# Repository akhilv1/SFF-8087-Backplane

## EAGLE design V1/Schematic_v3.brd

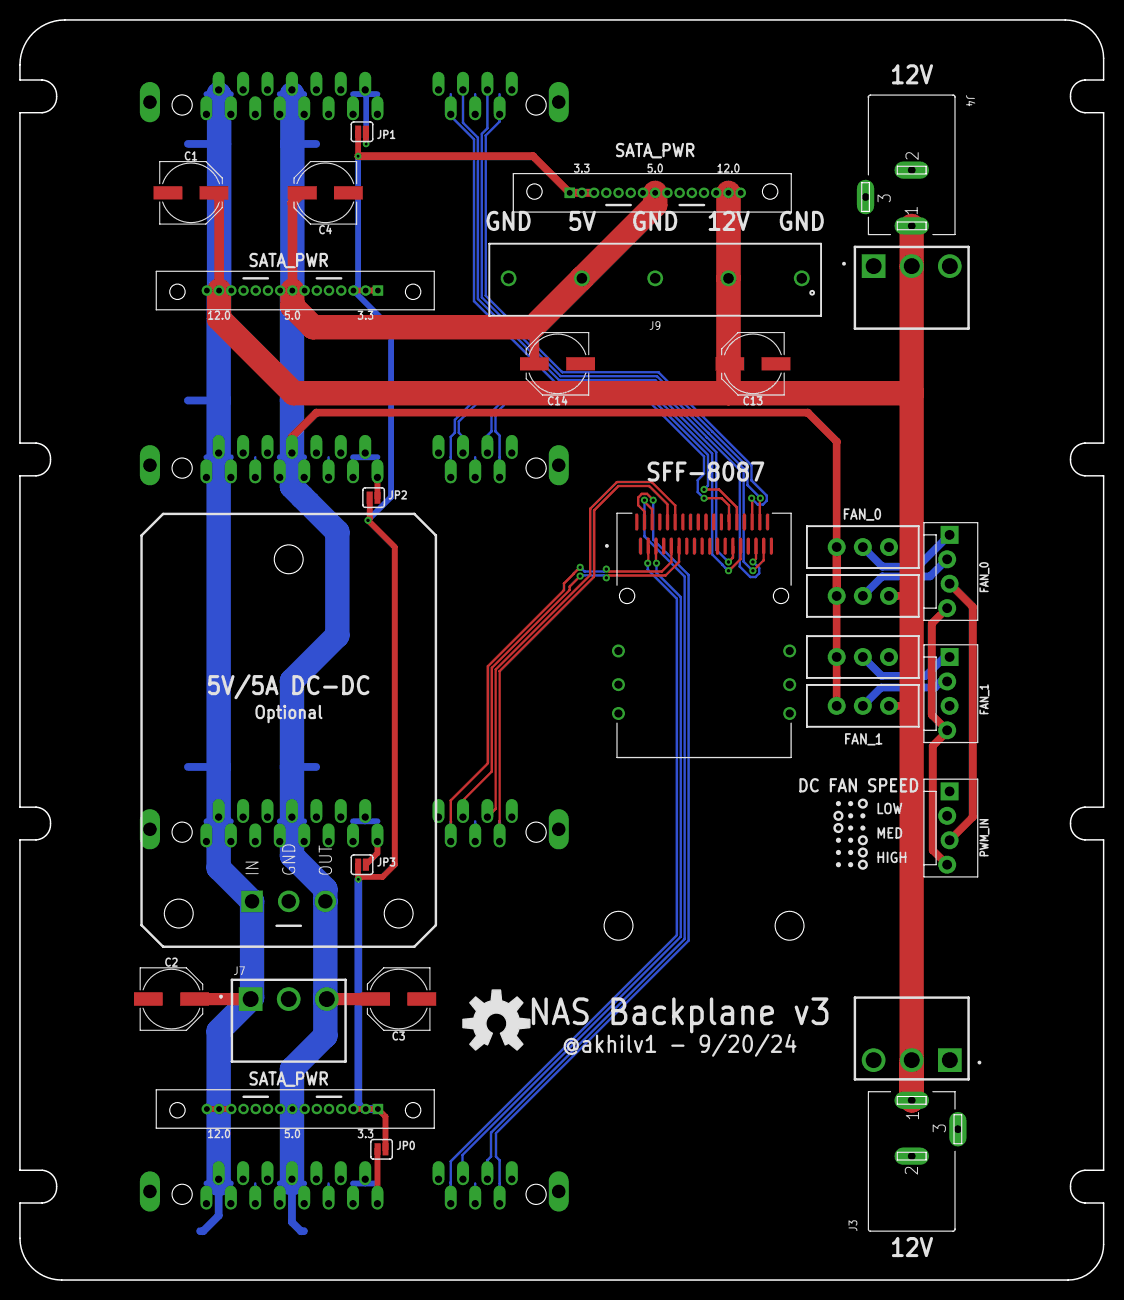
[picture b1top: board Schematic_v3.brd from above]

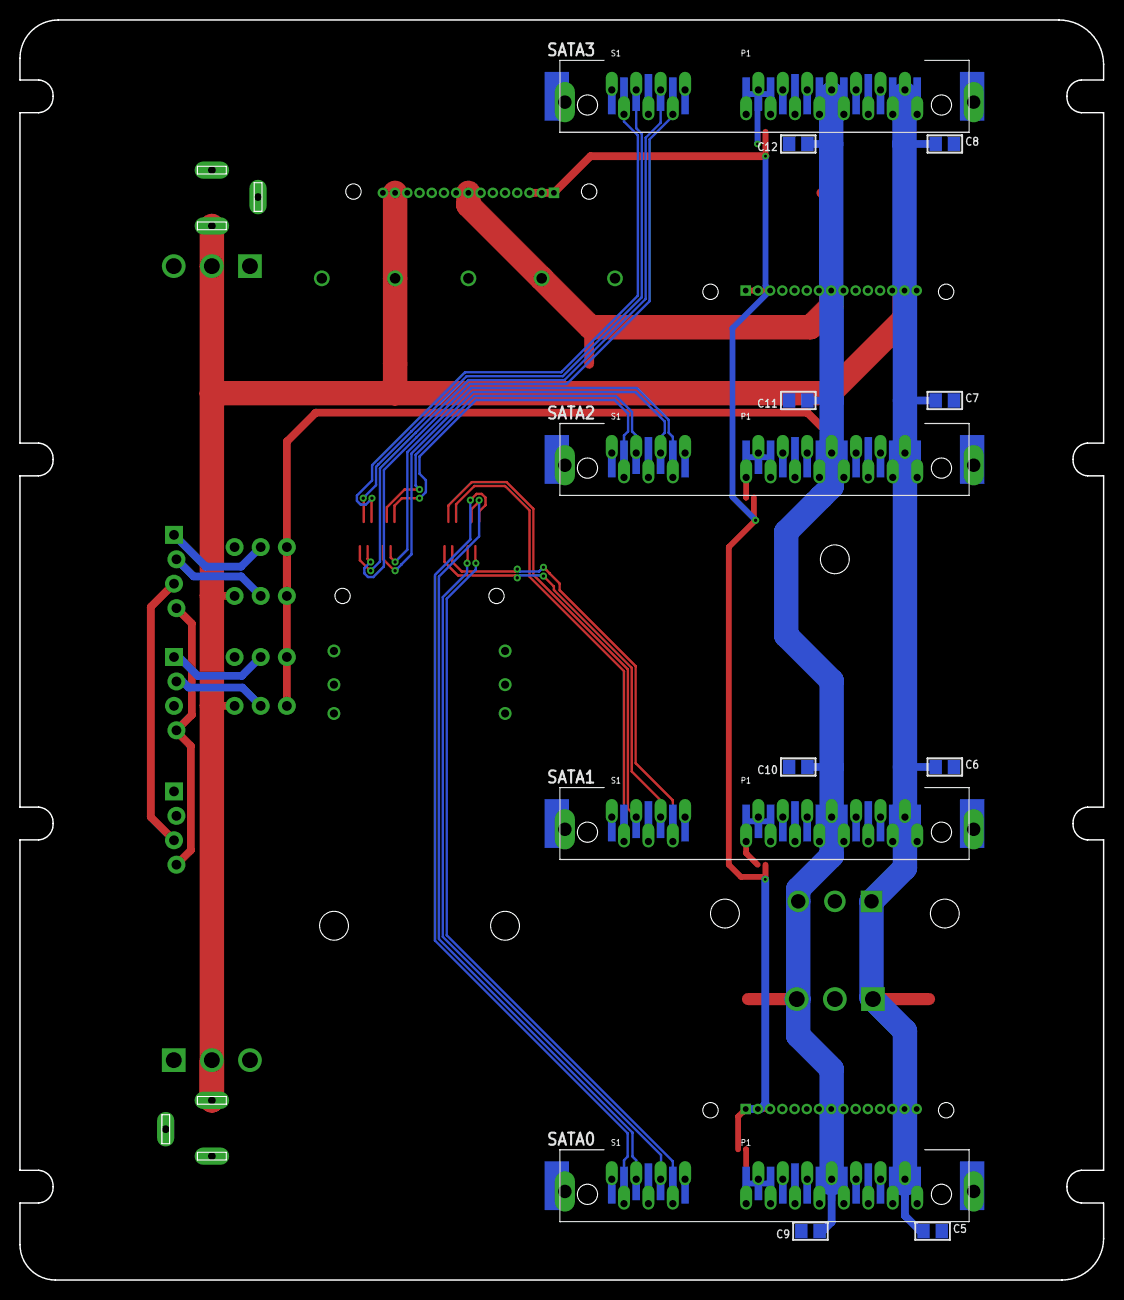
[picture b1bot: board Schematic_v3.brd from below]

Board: 2 copper layers, 112.7 x 131.0 mm, 41 parts (12 on the bottom side), 30 nets.

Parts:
C1, C2, C3, C4, C13, C14: 100uF; PANASONIC_D
C5, C6, C7, C8, C9, C10, C11, C12: C0805
FAN_0, FAN_1: MOLEX-1X4_LOCK
J1, J2, J8: SATAPWR; PTH_90
J3, J4: 694106301002
J5, J6, J7: B3P-VH(LF)(SN); HDR-03
J9: 691243410005
JP0, JP1, JP2, JP3: JUMPER-SMT_2_NC_PASTE_SILK; SMT-JUMPER_2_NC_PASTE_SILK
LOGO1: OSHW-LOGOL; OSHW-LOGO-L
PWM_IN: MOLEX-1X4_LOCK
S1, S2, S3, S4: SWITCH_SPDT_PTH_11.6X4.0MM_LOCK
SATA0, SATA1, SATA2, SATA3: 1735284-3; TE_2023246-2
SFF-8087: 1888019-4; TE_1888019-4
U$1: 5V_DC_DC; 5V_15W_DC_DC

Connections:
3.3V: J1.P$1, J1.P$2, J1.P$3, J2.P$1, J2.P$2, J2.P$3, J8.P$1, J8.P$2, J8.P$3, JP0.1, JP1.1, JP2.1, JP3.1
5V: C3.+, C4.+, C9.1, C10.1, C11.1, C12.1, C14.+, J1.P$7, J1.P$8, J1.P$9, J2.P$7, J2.P$8, J2.P$9, J7.3, J8.P$7, J8.P$8, J8.P$9, J9.4, S1.3, S2.1, S3.3, S4.1, SATA0.P7, SATA0.P8, SATA0.P9, SATA0.THT14, SATA0.THT15, SATA0.THT16, SATA1.P7, SATA1.P8, SATA1.P9, SATA1.THT14, SATA1.THT15, SATA1.THT16, SATA2.P7, SATA2.P8, SATA2.P9, SATA2.THT14, SATA2.THT15, SATA2.THT16, SATA3.P7, SATA3.P8, SATA3.P9, SATA3.THT14, SATA3.THT15, SATA3.THT16, U$1.P$3
12V: C1.+, C2.+, C5.1, C6.1, C7.1, C8.1, C13.+, J1.P$13, J1.P$14, J1.P$15, J2.P$13, J2.P$14, J2.P$15, J3.1, J4.1, J5.2, J6.2, J7.1, J8.P$13, J8.P$14, J8.P$15, J9.2, S1.1, S3.1, SATA0.P13, SATA0.P14, SATA0.P15, SATA0.THT20, SATA0.THT21, SATA0.THT22, SATA1.P13, SATA1.P14, SATA1.P15, SATA1.THT20, SATA1.THT21, SATA1.THT22, SATA2.P13, SATA2.P14, SATA2.P15, SATA2.THT20, SATA2.THT21, SATA2.THT22, SATA3.P13, SATA3.P14, SATA3.P15, SATA3.THT20, SATA3.THT21, SATA3.THT22, U$1.P$1
FAN0_HI: FAN_0.2, S1.2
FAN0_LO: FAN_0.1, S2.2
FAN1_HI: FAN_1.2, S3.2
FAN1_LO: FAN_1.1, S4.2
FAN_PWM: FAN_0.4, FAN_1.4, PWM_IN.4
FAN_TACH: FAN_0.3, PWM_IN.3
GND: C1.-, C2.-, C3.-, C4.-, C5.2, C6.2, C7.2, C8.2, C9.2, C10.2, C11.2, C12.2, C13.-, C14.-, J1.P$4, J1.P$5, J1.P$6, J1.P$10, J1.P$11, J1.P$12, J2.P$4, J2.P$5, J2.P$6, J2.P$10, J2.P$11, J2.P$12, J3.2, J4.2, J5.1, J5.3, J6.1, J6.3, J7.2, J8.P$4, J8.P$5, J8.P$6, J8.P$10, J8.P$11, J8.P$12, J9.1, J9.3, J9.5, PWM_IN.1, S2.3, S4.3, SATA0.P4, SATA0.P5, SATA0.P6, SATA0.P10, SATA0.P11, SATA0.P12, SATA0.P$1, SATA0.P$2, SATA0.S1, SATA0.S4, SATA0.S7, SATA0.THT1, SATA0.THT4, SATA0.THT7, SATA0.THT11, SATA0.THT12, SATA0.THT13, SATA0.THT17, SATA0.THT18, SATA0.THT19, SATA0.THT$1, SATA0.THT$2, SATA1.P4, SATA1.P5, SATA1.P6, SATA1.P10, SATA1.P11, SATA1.P12, SATA1.P$1, SATA1.P$2, SATA1.S1, SATA1.S4, SATA1.S7, SATA1.THT1, SATA1.THT4, SATA1.THT7, SATA1.THT11, SATA1.THT12, SATA1.THT13, SATA1.THT17, SATA1.THT18, SATA1.THT19, SATA1.THT$1, SATA1.THT$2, SATA2.P4, SATA2.P5, SATA2.P6, SATA2.P10, SATA2.P11, SATA2.P12, SATA2.P$1, SATA2.P$2, SATA2.S1, SATA2.S4, SATA2.S7, SATA2.THT1, SATA2.THT4, SATA2.THT7, SATA2.THT11, SATA2.THT12, SATA2.THT13, SATA2.THT17, SATA2.THT18, SATA2.THT19, SATA2.THT$1, SATA2.THT$2, SATA3.P4, SATA3.P5, SATA3.P6, SATA3.P10, SATA3.P11, SATA3.P12, SATA3.P$1, SATA3.P$2, SATA3.S1, SATA3.S4, SATA3.S7, SATA3.THT1, SATA3.THT4, SATA3.THT7, SATA3.THT11, SATA3.THT12, SATA3.THT13, SATA3.THT17, SATA3.THT18, SATA3.THT19, SATA3.THT$1, SATA3.THT$2, SFF-8087.A1, SFF-8087.A4, SFF-8087.A7, SFF-8087.A12, SFF-8087.A15, SFF-8087.A18, SFF-8087.B1, SFF-8087.B4, SFF-8087.B7, SFF-8087.B12, SFF-8087.B15, SFF-8087.B18, SFF-8087.S1, SFF-8087.S2, SFF-8087.S3, SFF-8087.S4, SFF-8087.S5, SFF-8087.S6, U$1.P$2
unnamed: JP1.2, SATA3.P1, SATA3.P2, SATA3.P3, SATA3.THT8, SATA3.THT9, SATA3.THT10
unnamed: JP2.2, SATA2.P1, SATA2.P2, SATA2.P3, SATA2.THT8, SATA2.THT9, SATA2.THT10
unnamed: JP3.2, SATA1.P1, SATA1.P2, SATA1.P3, SATA1.THT8, SATA1.THT9, SATA1.THT10
unnamed: JP0.2, SATA0.P1, SATA0.P2, SATA0.P3, SATA0.THT8, SATA0.THT9, SATA0.THT10
RX0_N: SATA0.S5, SATA0.THT5, SFF-8087.A3
RX0_P: SATA0.S6, SATA0.THT6, SFF-8087.A2
RX1_N: SATA1.S5, SATA1.THT5, SFF-8087.A6
RX1_P: SATA1.S6, SATA1.THT6, SFF-8087.A5
RX2_N: SATA2.S5, SATA2.THT5, SFF-8087.A14
RX2_P: SATA2.S6, SATA2.THT6, SFF-8087.A13
RX3_N: SATA3.S5, SATA3.THT5, SFF-8087.A17
RX3_P: SATA3.S6, SATA3.THT6, SFF-8087.A16
TX0_N: SATA0.S3, SATA0.THT3, SFF-8087.B3
TX0_P: SATA0.S2, SATA0.THT2, SFF-8087.B2
TX1_N: SATA1.S3, SATA1.THT3, SFF-8087.B6
TX1_P: SATA1.S2, SATA1.THT2, SFF-8087.B5
TX2_N: SATA2.S3, SATA2.THT3, SFF-8087.B14
TX2_P: SATA2.S2, SATA2.THT2, SFF-8087.B13
TX3_N: SATA3.S3, SATA3.THT3, SFF-8087.B17
TX3_P: SATA3.S2, SATA3.THT2, SFF-8087.B16

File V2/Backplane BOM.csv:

Qty,Value,Device,Parts,Description,Link
1,691243410005    ,691243410005    ,J9,7.62mm Pitch Rising Clamp Connector,
8,10uF,CAP_CERAMIC0805,"C5, C6, C7, C8, C9, C10, C11, C12",SMD Capacitors 0805 10uF,
3,,CONN_04POLAR_LOCK,"FAN_0, FAN_1, PWM_IN",Fan Headers 2.54mm Pitch,
4,,SWITCH-SPDT-PTH-11.6X4.0MM-LOCK,"S1, S2, S3, S4",Fan Mode Switches,
6,100uF,100UF-POLAR-25V-20%(ELEC),"C1, C2, C3, C4, C13, C14",100uF Electrolytic Capacitors,
4,1735284-3,TE_1735284-2,"SATA0, SATA1, SATA2, SATA3",Right Angle SATA Connectors,https://a.aliexpress.com/_mtHZzUZ
1,1888019-4,TE_1888019-4,SFF-8087,SFF-8087 SMD Connector,
1,39301060,39301060,POWER,Molex Mini-Fit JR 6-pin 90Deg,
1,5V_DC_DC,5V_DC_DC,BUCK,5v Step Down Converter (12v only input configuration),https://a.aliexpress.com/_mOm8TaH
1,694106301002    ,694106301002    ,J4,DC Barrel Power Jack 6.4mm Diam,
2,B3P-VH(LF)(SN),B3P-VH(LF)(SN),"J5, J7",JST-VH Connectors,
3,SATAPWR,SATAPWR,"J1, J2, J8",SATA Power Input Through Hole,https://a.aliexpress.com/_msddJj7

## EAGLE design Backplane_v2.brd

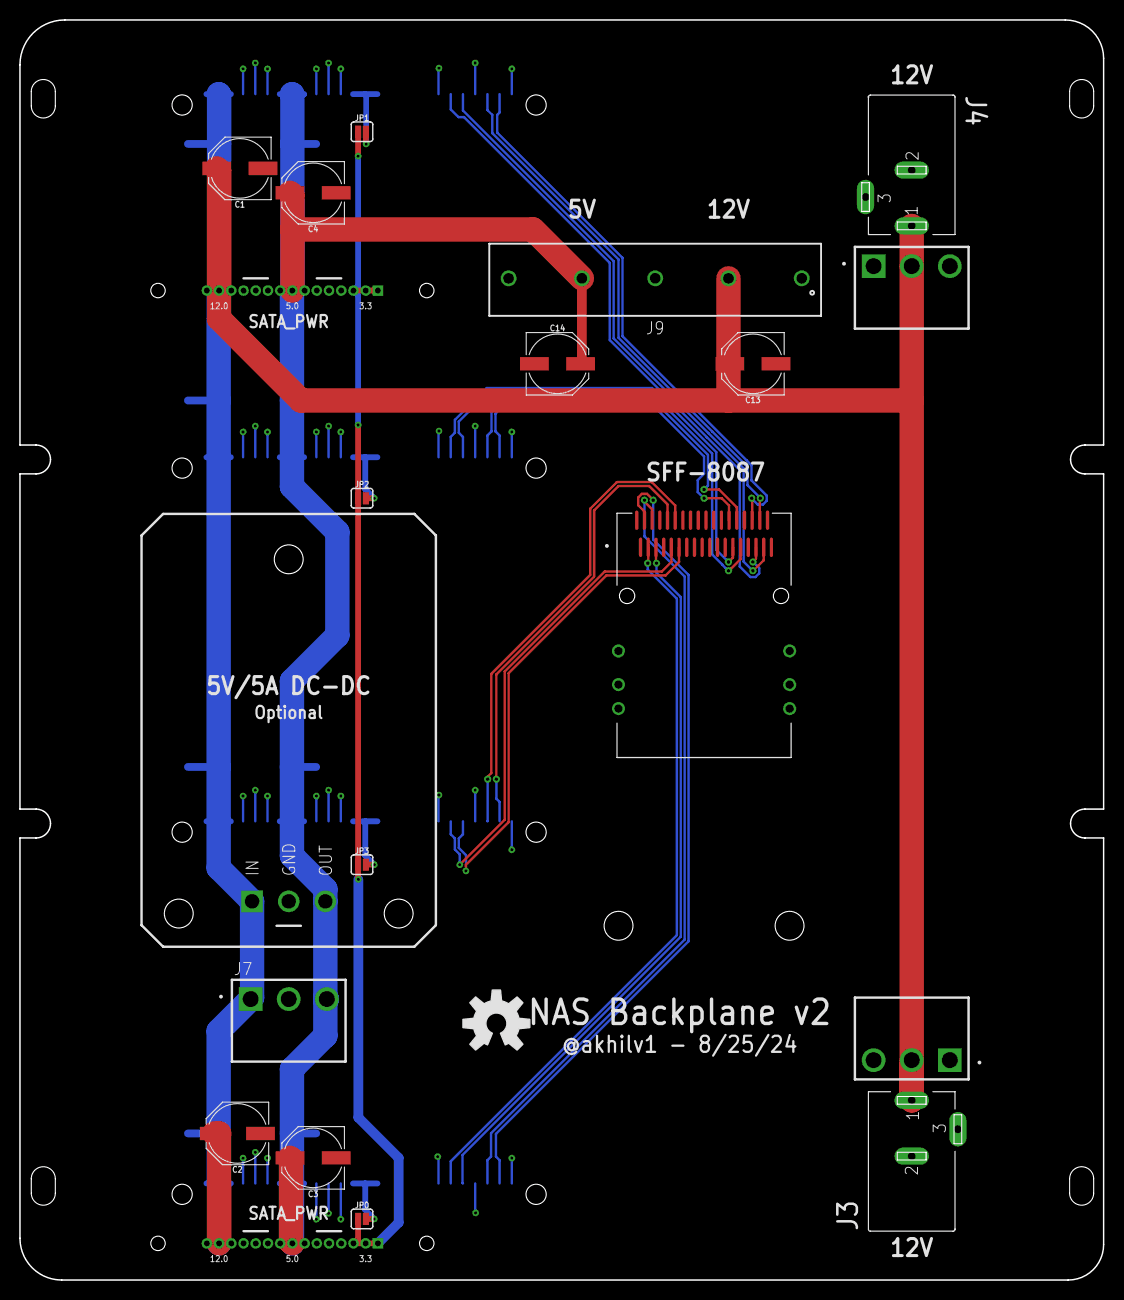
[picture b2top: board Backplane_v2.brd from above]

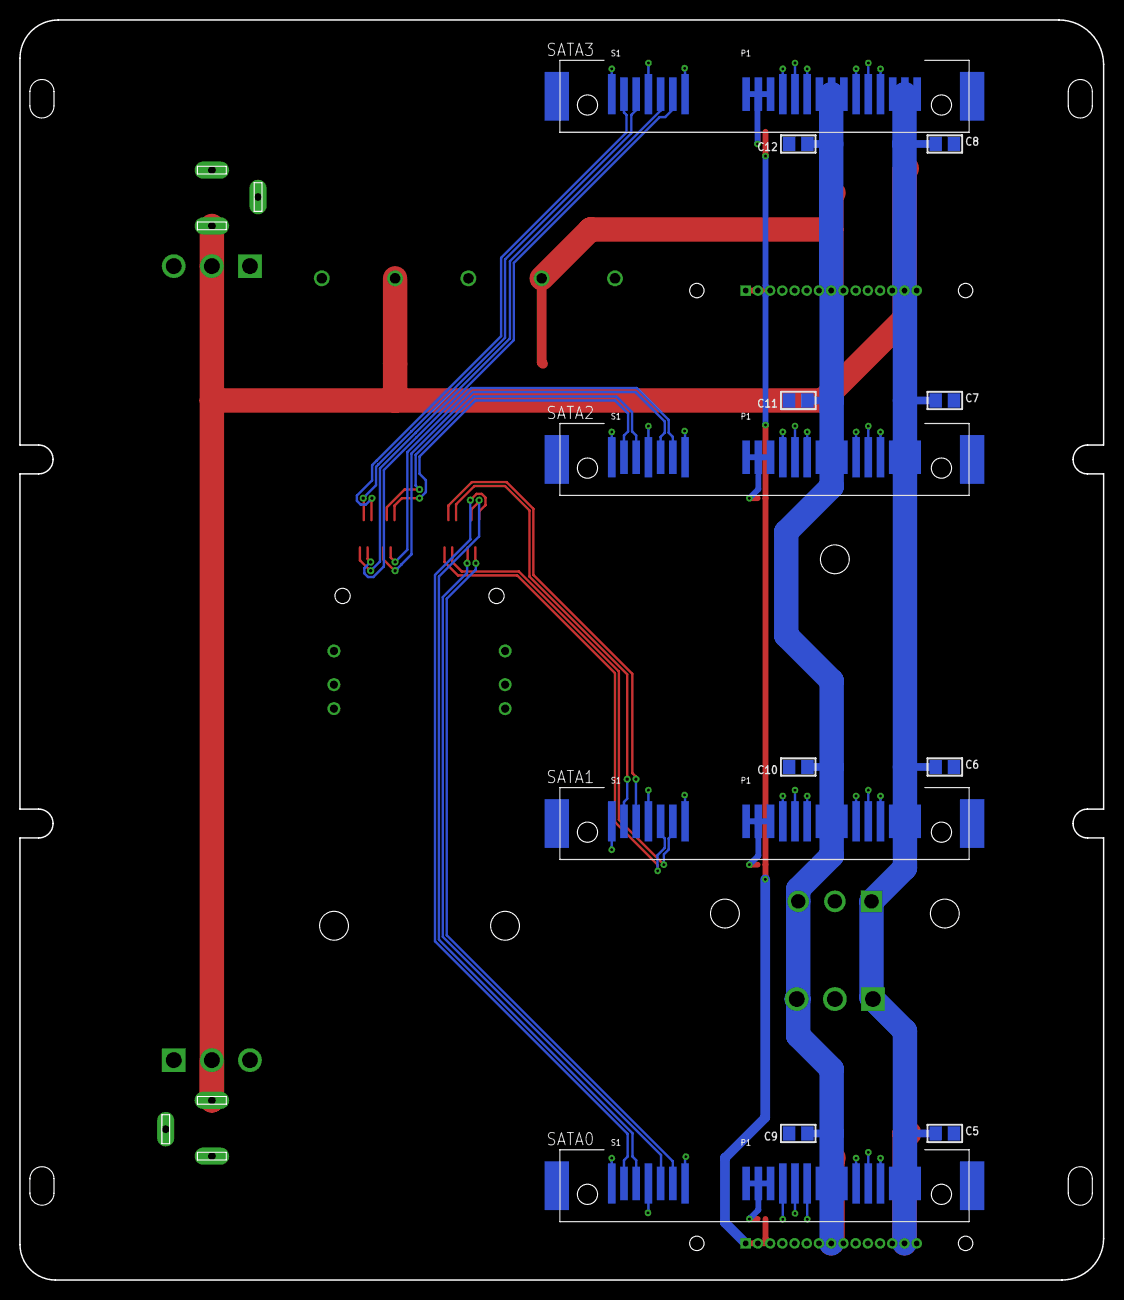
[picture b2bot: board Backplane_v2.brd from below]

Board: 2 copper layers, 112.7 x 131.0 mm, 33 parts (12 on the bottom side), 24 nets.

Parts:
C1, C2, C3, C4, C13, C14: 100uF; PANASONIC_D
C5, C6, C7, C8, C9, C10, C11, C12: C0805
J1, J2: SATAPWR; PTH_90
J3, J4: 694106301002
J5, J6, J7: B3P-VH(LF)(SN); HDR-03
J9: 691243410005
JP0, JP1, JP2, JP3: JUMPER-SMT_2_NC_PASTE_SILK; SMT-JUMPER_2_NC_PASTE_SILK
LOGO1: OSHW-LOGOL; OSHW-LOGO-L
SATA0, SATA1, SATA2, SATA3: 1735284-3; TE_2023246-2
SFF-8087: 1888019-4; TE_1888019-4
U$1: 5V_DC_DC; 5V_15W_DC_DC

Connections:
3.3V: J1.P$1, J1.P$2, J1.P$3, J2.P$1, J2.P$2, J2.P$3, JP0.1, JP1.1, JP2.1, JP3.1
5V: C3.+, C4.+, C9.1, C10.1, C11.1, C12.1, C14.+, J1.P$7, J1.P$8, J1.P$9, J2.P$7, J2.P$8, J2.P$9, J7.3, J9.4, SATA0.P7, SATA0.P8, SATA0.P9, SATA1.P7, SATA1.P8, SATA1.P9, SATA2.P7, SATA2.P8, SATA2.P9, SATA3.P7, SATA3.P8, SATA3.P9, U$1.P$3
12V: C1.+, C2.+, C5.1, C6.1, C7.1, C8.1, C13.+, J1.P$13, J1.P$14, J1.P$15, J2.P$13, J2.P$14, J2.P$15, J3.1, J4.1, J5.2, J6.2, J7.1, J9.2, SATA0.P13, SATA0.P14, SATA0.P15, SATA1.P13, SATA1.P14, SATA1.P15, SATA2.P13, SATA2.P14, SATA2.P15, SATA3.P13, SATA3.P14, SATA3.P15, U$1.P$1
GND: C1.-, C2.-, C3.-, C4.-, C5.2, C6.2, C7.2, C8.2, C9.2, C10.2, C11.2, C12.2, C13.-, C14.-, J1.P$4, J1.P$5, J1.P$6, J1.P$10, J1.P$11, J1.P$12, J2.P$4, J2.P$5, J2.P$6, J2.P$10, J2.P$11, J2.P$12, J3.2, J4.2, J5.1, J5.3, J6.1, J6.3, J7.2, J9.1, J9.3, J9.5, SATA0.P4, SATA0.P5, SATA0.P6, SATA0.P10, SATA0.P11, SATA0.P12, SATA0.P$1, SATA0.P$2, SATA0.S1, SATA0.S4, SATA0.S7, SATA1.P4, SATA1.P5, SATA1.P6, SATA1.P10, SATA1.P11, SATA1.P12, SATA1.P$1, SATA1.P$2, SATA1.S1, SATA1.S4, SATA1.S7, SATA2.P4, SATA2.P5, SATA2.P6, SATA2.P10, SATA2.P11, SATA2.P12, SATA2.P$1, SATA2.P$2, SATA2.S1, SATA2.S4, SATA2.S7, SATA3.P4, SATA3.P5, SATA3.P6, SATA3.P10, SATA3.P11, SATA3.P12, SATA3.P$1, SATA3.P$2, SATA3.S1, SATA3.S4, SATA3.S7, SFF-8087.A1, SFF-8087.A4, SFF-8087.A7, SFF-8087.A12, SFF-8087.A15, SFF-8087.A18, SFF-8087.B1, SFF-8087.B4, SFF-8087.B7, SFF-8087.B12, SFF-8087.B15, SFF-8087.B18, SFF-8087.S1, SFF-8087.S2, SFF-8087.S3, SFF-8087.S4, SFF-8087.S5, SFF-8087.S6, U$1.P$2
unnamed: JP1.2, SATA3.P1, SATA3.P2, SATA3.P3
unnamed: JP2.2, SATA2.P1, SATA2.P2, SATA2.P3
unnamed: JP3.2, SATA1.P1, SATA1.P2, SATA1.P3
unnamed: JP0.2, SATA0.P1, SATA0.P2, SATA0.P3
RX0_N: SATA0.S5, SFF-8087.A3
RX0_P: SATA0.S6, SFF-8087.A2
RX1_N: SATA1.S5, SFF-8087.A6
RX1_P: SATA1.S6, SFF-8087.A5
RX2_N: SATA2.S5, SFF-8087.A14
RX2_P: SATA2.S6, SFF-8087.A13
RX3_N: SATA3.S5, SFF-8087.A17
RX3_P: SATA3.S6, SFF-8087.A16
TX0_N: SATA0.S3, SFF-8087.B3
TX0_P: SATA0.S2, SFF-8087.B2
TX1_N: SATA1.S3, SFF-8087.B6
TX1_P: SATA1.S2, SFF-8087.B5
TX2_N: SATA2.S3, SFF-8087.B14
TX2_P: SATA2.S2, SFF-8087.B13
TX3_N: SATA3.S3, SFF-8087.B17
TX3_P: SATA3.S2, SFF-8087.B16

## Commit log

2024-08-29 Initial commit of v2 backplane files
2024-09-20 Added V3 Backplane
2025-08-18 Add V2 Files
2025-08-18 Add Gerber files for backplane variants

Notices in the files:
parts and their libraries:
SparkFun-Capacitors: Licensing: Creative Commons ShareAlike 4.0 International - https://creativecommons.org/licenses/by-sa/4.0
Wurth_Connectors_WR-TBL Rising Cage Clam: Copyright: Würth Elektronik
